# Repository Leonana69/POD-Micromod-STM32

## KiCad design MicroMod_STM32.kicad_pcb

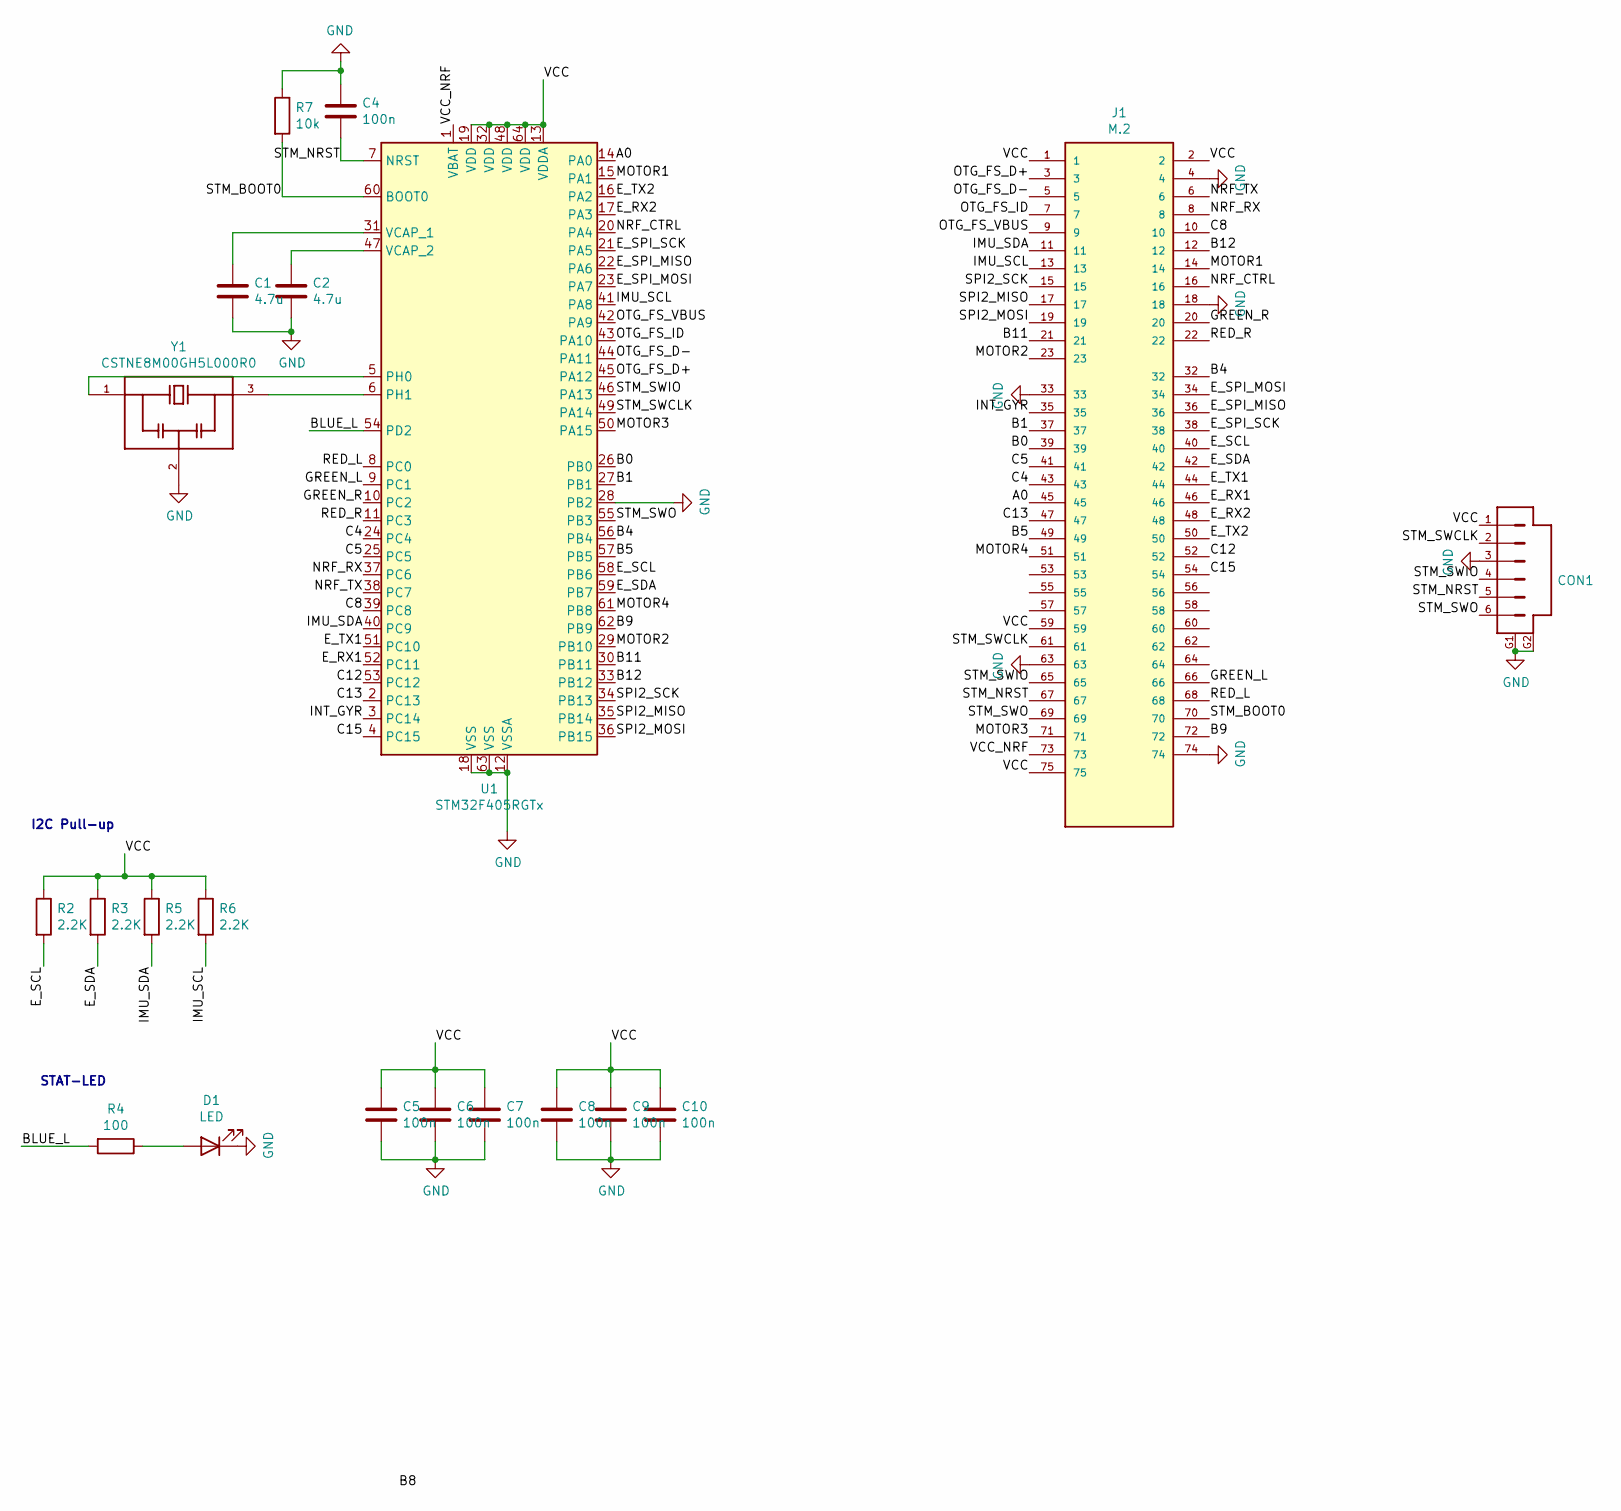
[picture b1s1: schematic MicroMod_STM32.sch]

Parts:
C1, C2: 4.7u; 0402-TIGHT
C4, C5, C6, C7, C8, C9, C10: 100n; 0402-TIGHT
CON1: SM06B-SRSS-TB; SM06B; DIGIKEY# 455-1806-1-ND
D1: LED; LED-0603
J1: M.2; M.2-CARD-E-22
R2, R3, R5, R6: 2.2K; 0402-TIGHT
R4: 100; 0402-TIGHT
R7: 10k; 0402-TIGHT
U1: STM32F405RGTx; TQFP64
Y1: CSTNE8M00GH5L000R0; OSC_CSTNE8M00GH5L000R0; PARTREV JGC42-8858A

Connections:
/A0: J1.45, U1.14 (PA0)
/B0: J1.39, U1.26 (PB0)
/B1: J1.37, U1.27 (PB1)
/B4: J1.32, U1.56 (PB4)
/B5: J1.49, U1.57 (PB5)
/B9: J1.72, U1.62 (PB9)
/B11: J1.21, U1.30 (PB11)
/B12: J1.12, U1.33 (PB12)
/BLUE_L: R4.2, U1.54 (PD2)
/C4: J1.43, U1.24 (PC4)
/C5: J1.41, U1.25 (PC5)
/C8: J1.10, U1.39 (PC8)
/C12: J1.52, U1.53 (PC12)
/C13: J1.47, U1.2 (PC13)
/C15: J1.54, U1.4 (PC15)
/E_RX1: J1.46, U1.52 (PC11)
/E_RX2: J1.48, U1.17 (PA3)
/E_SCL: J1.40, R2.2, U1.58 (PB6)
/E_SDA: J1.42, R3.2, U1.59 (PB7)
/E_SPI_MISO: J1.36, U1.22 (PA6)
/E_SPI_MOSI: J1.34, U1.23 (PA7)
/E_SPI_SCK: J1.38, U1.21 (PA5)
/E_TX1: J1.44, U1.51 (PC10)
/E_TX2: J1.50, U1.16 (PA2)
/GREEN_L: J1.66, U1.9 (PC1)
/GREEN_R: J1.20, U1.10 (PC2)
/IMU_SCL: J1.13, R6.2, U1.41 (PA8)
/IMU_SDA: J1.11, R5.2, U1.40 (PC9)
/INT_GYR: J1.35, U1.3 (PC14)
/MOTOR1: J1.14, U1.15 (PA1)
/MOTOR2: J1.23, U1.29 (PB10)
/MOTOR3: J1.71, U1.50 (PA15)
/MOTOR4: J1.51, U1.61 (PB8)
/NRF_CTRL: J1.16, U1.20 (PA4)
/NRF_RX: J1.8, U1.37 (PC6)
/NRF_TX: J1.6, U1.38 (PC7)
/OTG_FS_D+: J1.3, U1.45 (PA12)
/OTG_FS_D-: J1.5, U1.44 (PA11)
/OTG_FS_ID: J1.7, U1.43 (PA10)
/OTG_FS_VBUS: J1.9, U1.42 (PA9)
/RED_L: J1.68, U1.8 (PC0)
/RED_R: J1.22, U1.11 (PC3)
/SPI2_MISO: J1.17, U1.35 (PB14)
/SPI2_MOSI: J1.19, U1.36 (PB15)
/SPI2_SCK: J1.15, U1.34 (PB13)
/STM_BOOT0: J1.70, R7.2, U1.60 (BOOT0)
/STM_NRST: C4.2, CON1.5, J1.67, U1.7 (NRST)
/STM_SWCLK: CON1.2, J1.61, U1.49 (PA14)
/STM_SWIO: CON1.4, J1.65, U1.46 (PA13)
/STM_SWO: CON1.6, J1.69, U1.55 (PB3)
/VCC: C5.1, C6.1, C7.1, C8.1, C9.1, C10.1, CON1.1, J1.1, J1.2, J1.59, J1.75, R2.1, R3.1, R5.1, R6.1, U1.13 (VDDA), U1.19 (VDD), U1.32 (VDD), U1.48 (VDD), U1.64 (VDD)
/VCC_NRF: J1.73, U1.1 (VBAT)
GND: C1.2, C2.2, C4.1, C5.2, C6.2, C7.2, C8.2, C9.2, C10.2, CON1.3, CON1.G1, CON1.G2, D1.1 (K), J1.4, J1.18, J1.33, J1.63, J1.74, R7.1, U1.12 (VSSA), U1.18 (VSS), U1.28 (PB2), U1.63 (VSS), Y1.2
unnamed: C1.1, U1.31 (VCAP_1)
unnamed: C2.1, U1.47 (VCAP_2)
unnamed: D1.2 (A), R4.1
unnamed: U1.5 (PH0), Y1.1
unnamed: U1.6 (PH1), Y1.3

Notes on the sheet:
I2C Pull-up
STAT-LED

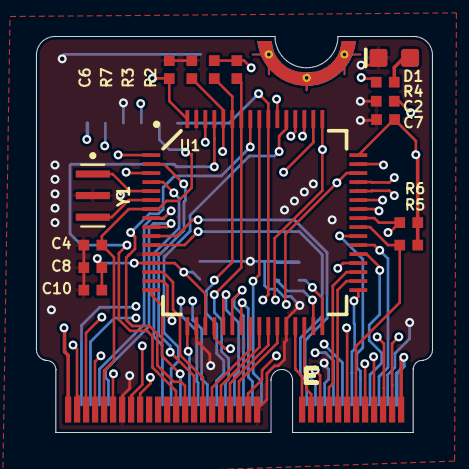
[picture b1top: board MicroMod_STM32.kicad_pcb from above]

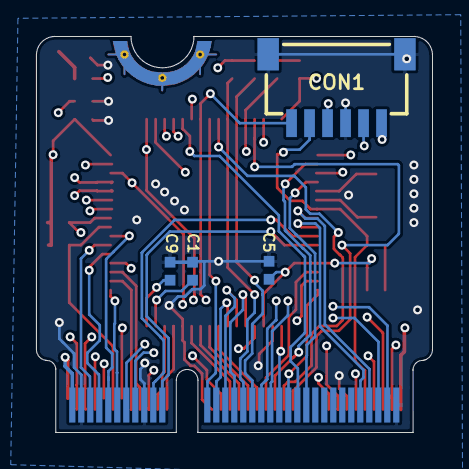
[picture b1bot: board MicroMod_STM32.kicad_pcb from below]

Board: 4 copper layers, 22.0 x 22.0 mm, 20 parts (4 on the bottom side), 58 nets.

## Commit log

2021-10-22 init file
2021-10-23 version 1
2021-10-24 update nothing
2021-10-25 no track under oscillator
2021-10-25 update vbat line
2021-10-26 update vcc copper
2021-11-19 MOTOR4 -> PB10
2021-11-19 MOTOR2->PB10,MOTOR4->PB8
